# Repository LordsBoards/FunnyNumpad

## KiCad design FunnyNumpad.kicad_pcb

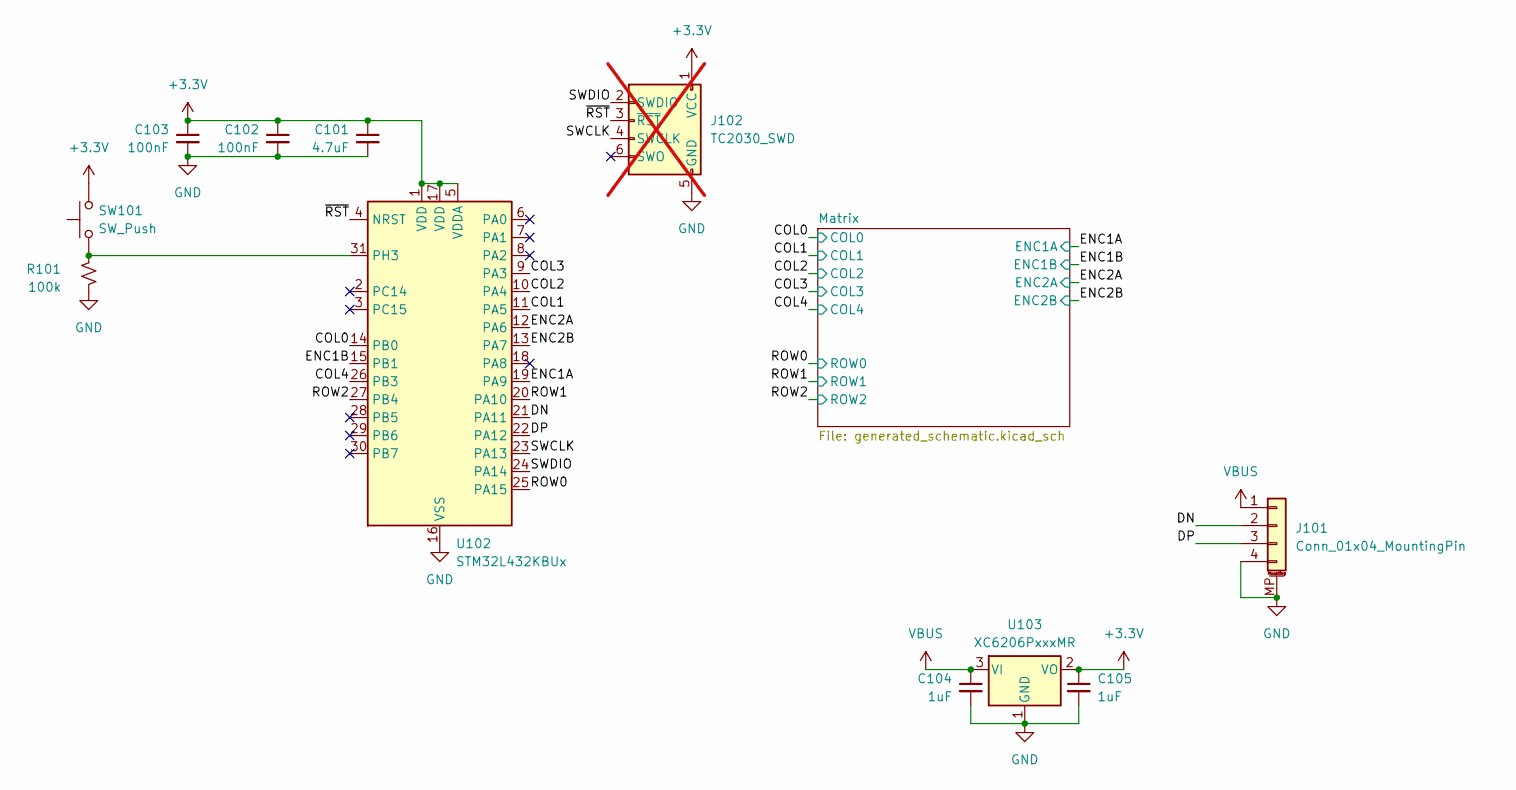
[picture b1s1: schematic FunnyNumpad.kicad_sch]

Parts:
C101: 4.7uF; C_0402_1005Metric; LCSC C23733
C102, C103: 100nF; C_0402_1005Metric; LCSC C1525
C104, C105: 1uF; C_0402_1005Metric; LCSC C52923
J101: Conn_01x04_MountingPin; JST_SH_SM04B-SRSS-TB_1x04-1MP_P1.00mm_Horizontal; LCSC C7433425
J102: TC2030_SWD; CON_TC2030_outlined; not fitted
R101: 100k; R_0402_1005Metric; LCSC C106234
SW101: SW_Push; SW_Push_1P1T_XKB_TS-1187A; LCSC C318884
U102: STM32L432KBUx; QFN-32-1EP_5x5mm_P0.5mm_EP3.45x3.45mm_ThermalVias; LCSC C94784
U103: XC6206PxxxMR; SOT-23-3; LCSC C5446

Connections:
+3.3V: C101.1, C102.1, C103.1, C105.1, J102.1 (VCC), SW101.2, U102.1 (VDD), U102.5 (VDDA), U102.17 (VDD), U103.2 (VO); also elsewhere on the board
/COL0: U102.14 (PB0); also elsewhere on the board
/COL1: U102.11 (PA5); also elsewhere on the board
/COL2: U102.10 (PA4); also elsewhere on the board
/COL3: U102.9 (PA3); also elsewhere on the board
/COL4: U102.26 (PB3); also elsewhere on the board
/DN: J101.2, U102.21 (PA11)
/DP: J101.3, U102.22 (PA12)
/ENC1A: U102.19 (PA9); also elsewhere on the board
/ENC1B: U102.15 (PB1); also elsewhere on the board
/ENC2A: U102.12 (PA6); also elsewhere on the board
/ENC2B: U102.13 (PA7); also elsewhere on the board
/ROW0: U102.25 (PA15); also elsewhere on the board
/ROW1: U102.20 (PA10); also elsewhere on the board
/ROW2: U102.27 (PB4); also elsewhere on the board
/SWCLK: J102.4 (SWCLK), U102.23 (PA13)
/SWDIO: J102.2 (SWDIO), U102.24 (PA14)
/~RST: J102.3 (~RST), U102.4 (NRST)
GND: C101.2, C102.2, C103.2, C104.2, C105.2, J101.4, J101.MP (MountPin), J102.5 (GND), R101.1, U102.16 (VSS), U102.32 (VSS), U102.33 (VSS), U103.1 (GND); also elsewhere on the board
unnamed: R101.2, SW101.1, U102.31 (PH3)
VBUS: C104.1, J101.1, U103.3 (VI)

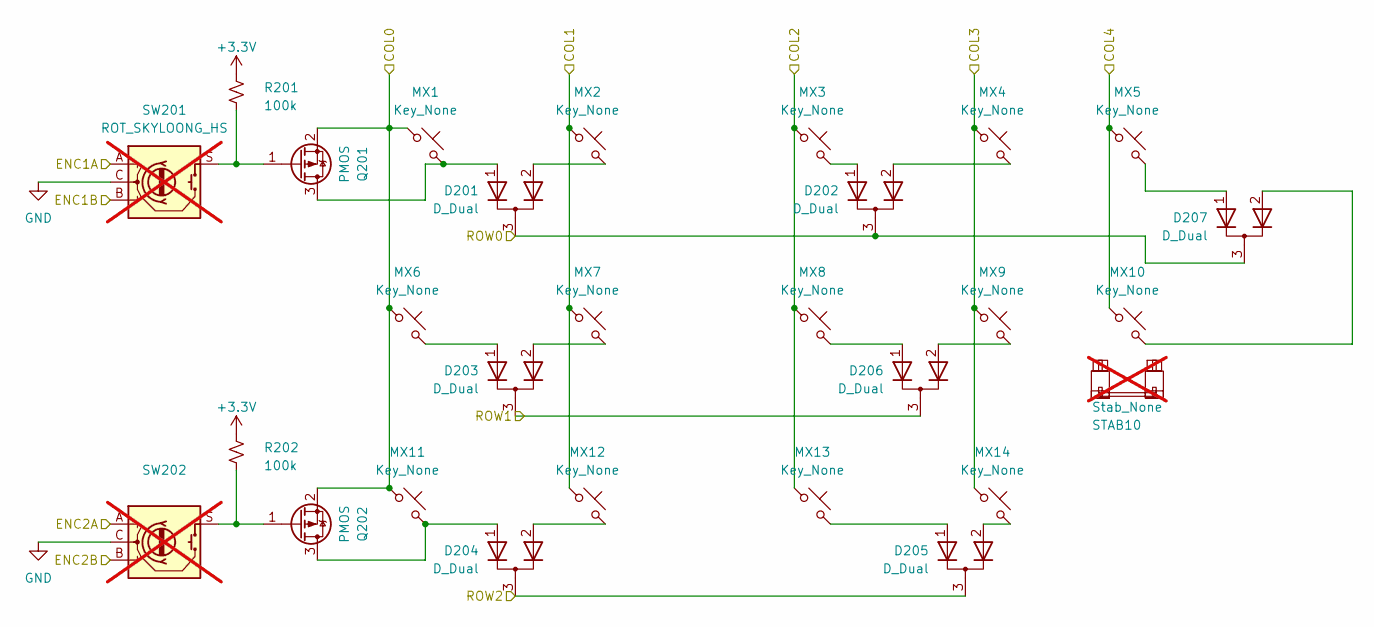
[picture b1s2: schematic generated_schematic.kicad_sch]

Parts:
D201, D202, D203, D204, D205, D206, D207: D_Dual; SOT-23; LCSC C68978
MX1, MX2, MX3, MX4, MX7, MX8, MX9, MX10, MX11, MX13, MX14: Key_None; SW_MX_HS_CPG151101S11_1u; LCSC C5156480
MX5: Key_None; SW_MX_HS_CPG151101S11_1.75u; LCSC C5156480
MX6: Key_None; SW_MX_HS_CPG151101S11_1.25u; LCSC C5156480
MX12: Key_None; SW_MX_HS_CPG151101S11_1.5u; LCSC C5156480
Q201, Q202: PMOS; SOT-23; LCSC C99272
R201, R202: 100k; R_0402_1005Metric; LCSC C106234
STAB10: Stab_None; STAB_MX_P_ISO; not fitted
SW201, SW202: ROT_SKYLOONG_HS; ROT_SKYLOONG_HS-Switch; not fitted

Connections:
+3.3V: R201.2, R202.2; also elsewhere on the board
/COL0: MX1.1, MX6.1, MX11.1, Q201.2 (S), Q202.2 (S); also elsewhere on the board
/COL1: MX2.1, MX7.1, MX12.1; also elsewhere on the board
/COL2: MX3.1, MX8.1, MX13.1; also elsewhere on the board
/COL3: MX4.1, MX9.1, MX14.1; also elsewhere on the board
/COL4: MX5.1, MX10.1; also elsewhere on the board
/ENC1A: SW201.A; also elsewhere on the board
/ENC1B: SW201.B; also elsewhere on the board
/ENC2A: SW202.A; also elsewhere on the board
/ENC2B: SW202.B; also elsewhere on the board
/ROW0: D201.3 (A), D202.3 (A), D207.3 (A); also elsewhere on the board
/ROW1: D203.3 (A), D206.3 (A); also elsewhere on the board
/ROW2: D204.3 (A), D205.3 (A); also elsewhere on the board
GND: SW201.C, SW202.C; also elsewhere on the board
unnamed: D201.2 (K), MX2.2
unnamed: D202.1 (K), MX3.2
unnamed: D202.2 (K), MX4.2
unnamed: D203.1 (K), MX6.2
unnamed: D203.2 (K), MX7.2
unnamed: D204.2 (K), MX12.2
unnamed: D205.1 (K), MX13.2
unnamed: D205.2 (K), MX14.2
unnamed: D206.1 (K), MX8.2
unnamed: D206.2 (K), MX9.2
unnamed: D207.1 (K), MX5.2
unnamed: D207.2 (K), MX10.2
unnamed: D201.1 (K), MX1.2, Q201.3 (D)
unnamed: Q201.1 (G), R201.1, SW201.S
unnamed: D204.1 (K), MX11.2, Q202.3 (D)
unnamed: Q202.1 (G), R202.1, SW202.S

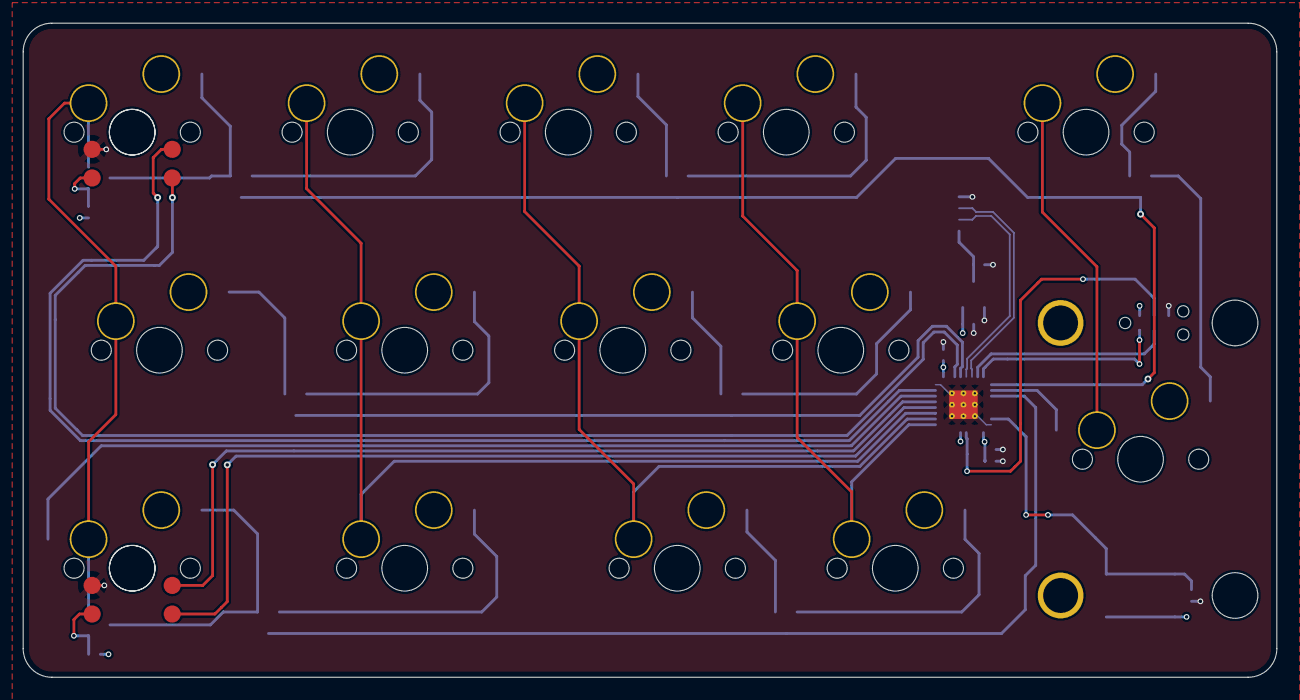
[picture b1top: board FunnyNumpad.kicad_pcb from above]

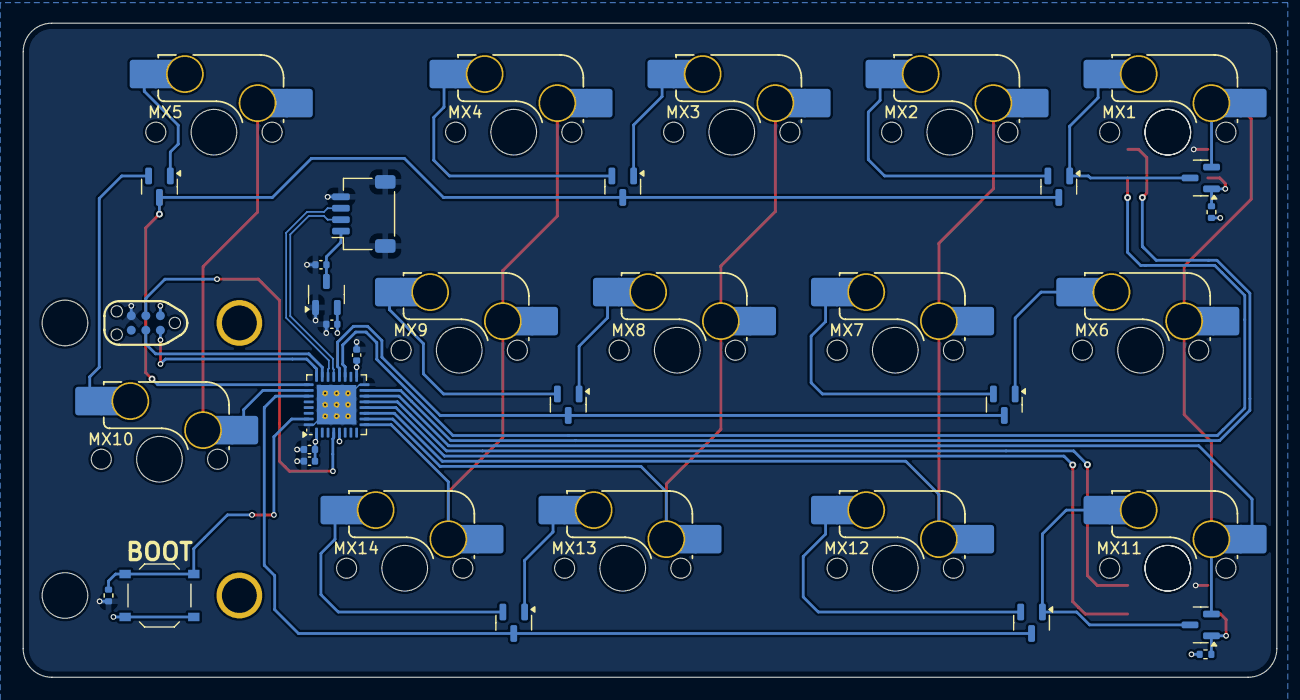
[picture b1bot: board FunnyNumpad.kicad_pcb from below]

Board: 4 copper layers, 109.5 x 57.1 mm, 39 parts (36 on the bottom side), 37 nets.
